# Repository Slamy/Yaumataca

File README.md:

# Yet another USB mouse and joystick to Amiga, Atari ST &amp; C64 Adapter

Or in short Yaumataca. This device allows to use modern USB input devices
on 80s style home computer controller ports. Being mechanical in nature, old gamepads and mouses
degrade over time and replacements using modern variants might be required.

This solution makes use of the Raspberry Pi Pico board (RP2040) which offers a dedicated USB host controller
and can be bought at a rather low price (5-8€ per unit).
Cheap NPN transistors are used for level shifting as the RP2040 is not 5V tolerant.

## How to use

The Yaumataca acts as both Joystick and Mouse. Plug both output ports into both controller ports of the target machine.
Plug a USB OTG Hub into the Micro-USB port of the Pico board. Insert USB gamepad and USB mouse.

As multiple modes are supported, the [user manual](doc/user_manual.md) provides more detail.

## Features
* Cheap to build
* Uses "off the shelf" hardware
* Multiple USB devices on 2 Atari type controller ports using a single unit
* Primary joystick on left port
* Primary mouse on right port
* Amiga mouse with wheel using [WheelBusMouse](http://aminet.net/package/util/mouse/WheelBusMouse) driver
* Commodore 1351 in proportional mode
* Atari ST mouse
* Automatic switch between mouses and joysticks
* Swap of controller ports (useful for C64 games)
* Supports 2 mouses and 2 joysticks (useful for Lemmings and Marble Madness)
* Supports secondary fire button (Amiga and C64 style)
* Auto fire
* Configured mouse type is saved in flash

## Restrictions
* Only dedicated Joysticks are supported.
	* PS3 DualShock
	* PS4 DualShock
	* Nintendo Switch Pro Controller
	* Xbox 360 Wireless Receiver (1 or 2 controllers with one receiver)
	* Xbox One Controller
	* Xbox Series S/X Controller
	* Mega World International - USB Game Controllers (07b5:0314)
	* DragonInc Hizue Gamepad (0079:0011)

## TODO
* Amiga Mode: Add support for newmouse or Micromys protocol
	* Avoids necessity for manipulation of the unrelated joystick port
* Add 3. Fire button for more gamepads
* HID Descriptor Parsing (generic USB joystick support, eventually)
* Bluetooth (eventually)
* Explain C1351 calibration using C64 tool

## How to construct

The project is constructable via perfboard or PCB.

[Manual for construction on a perfboard](doc/construction_perfboard.md)

For the PCB, please use the [KiCad files](schematic/yaumataca/).
If you order your parts from [Reichelt](https//reichelt.de), you may use the
attached [ordering lists](doc/reichelt.csv) which can be imported on the website.

In case the PCB is chosen, there is also a [3D model of a case](housing/) available, which can be used for 3D printing.

To operate the unit, one OTG Hub is recommended which provides multiple USB A ports attached to a USB micro port.
If only one USB device is to be attached, a simple USB micro to USB A adapter will also work, but I suggest to go for the Hub.

### Example hardware design

Here an example of the PCB inside the case.

Here the PCB side by side with the prototype.

## How to build the firmware

Ensure that the submodules are also cloned.

	git submodule update --init --recursive
	mkdir build
	cd build
	cmake ..
	make

Alternatively there is also a small script which builds and packages the software as a zip file for upload.

	./scripts/build_release.sh

## How to flash

### Integrated USB bootloader

The RP2040 can be flashed using SWD or using the integrated USB bootloader.
As not everyone might have a debugger lying around, flash the Pico as so:

* Don't have the Pico board powered and connected.
* Press and hold the BOOTSEL button
* Connect the Pico to your PC while holding the button
* The Pico should be detected as mass storage device
* Copy `yaumataca.uf2` from the `build` folder to the device
* The LED of the Pico should start blinking

The Yaumataca is now ready for operation

### With SWD

This assumes that you are using a CMSIS-DAP compatible programmer. It is suggested to use a second Pico board as one.
This is possible using [the Picoprobe firmware](https://github.com/raspberrypi/picoprobe/releases).
Keep in mind that an st-link cannot be used with the RP2040, even so both speak SWD.

	openocd -f interface/cmsis-dap.cfg -f target/rp2040.cfg -c "adapter speed 20000; program build/yaumataca.elf verify reset exit"

Connect the picoprobe like so, to flash and debug the Yaumataca in standalone operation:

Keep in mind to only connect 5V (purple wire) when operating the Yaumataca without any home computer attached!
The 5V power supply is usually provided by the controller port and not from the PC!
It must not be delivered by both the developer PC and the homecomputer at the same time!

## Recommended IDE

Please use vscode and open the root folder with it.
This gives access to the already existing debugging targets.

## System architecture

## Doxygen and Unittests

It is my goal to have everything properly documented and tested

	scripts/check_doxygen.sh
	scripts/unittest.sh

## FAQ

### My gamepad is not supported. What can I do?

It depends. Some USB Gamepads are not following the HID standard, which is a huge
issue. The PS4 Controller is one rare exception which just works.
Bad examples are the Xbox One Controller and the Nintendo Switch Pro Controller.

Both require some sort of handshaking to activate the data transfer.

If you are lucky, you have a USB input device which just follows the HID standard.

[Please follow this guide to add additional gamepads](doc/adding_gamepads.md)

### I can see PRINTF all over the place. Where is the output going to?

This project makes use of "Segger RTT" which stores printed characters
inside a small buffer which can be displayed over SWD.
It has advantages compared to the UART as no additional GPIOs
have to be reserved for this.

I don't recommend to use rtthost as it is slow. Please use VSCode instead.

	rtthost -c rp2040

There is also pyocd available, which is faster:

	pyocd rtt --target rp2040

### SWD is failing with "Info : DAP init failed"

You have accidentally downloaded `debugprobe` and not `picoprobe`.
This project uses the CMSIS-DAP variant of the picoprobe!
One working version is [this one](https://github.com/raspberrypi/debugprobe/releases/tag/picoprobe-cmsis-v1.1).

### I can't use the C1351 mouse on "Final Cartridge III"

The design of the Yaumataca circuit might not be optimal, as it causes issues with the
way the FC3 software is using the SID muxes in desktop mode. For some reason, both Controller Ports
are muxed at the same time to the SIDs POT lines, so it can accept a mouse at either of the ports
without additional configuration. This however means that no two mice are allowed to be connected
at the same time.

The Yaumataca design is not aware of this and uses a 10k pullup on POT X and POT Y to charge the measurement capacitor.
This alone is not an issue. However, with the addition of the secondary fire buttons on the C64,
this indeed causes issues as the high state is the pressed state while the grounded state
is not pressed. This is opposite to how the Amiga handles its buttons.

If this issue occurs, just disconnect one of the controller ports.

### Why is this not written in Rust?

Because USB Host Support for the RP2040 is not yet awesome

### Isn't this yet another USB mouse and joystick to Amiga, Atari ST & C64 adapter

Exactly

### Funny anecdote

The popularity of this project was increased dramatically just becausean Atari ST
user was missing a mouse on a Commodore 64 party.
This happened on the DoReCo (Dortmund Retro Computer) Party 2024 in Anröche, Germany.

## Sources of Inspiration

My old project this here needs to surpass:<br>
http://slamyslab.blogspot.com/2013/02/pcbs-for-usb-datasette-and.html

Infos about Mouse Wheels on the Amiga:<br>
http://bax.comlab.uni-rostock.de/en/hardware/amiga-usb-mouse/

For the pinout:<br>
https://www.c64-wiki.de/wiki/Maus

Information about the Commodore 1351:<br>
http://sensi.org/~svo/%5Bm%5Douse/

Micromys C64 and Amiga Mouse Protocol:<br>
https://wiki.icomp.de/wiki/Micromys_Protocol

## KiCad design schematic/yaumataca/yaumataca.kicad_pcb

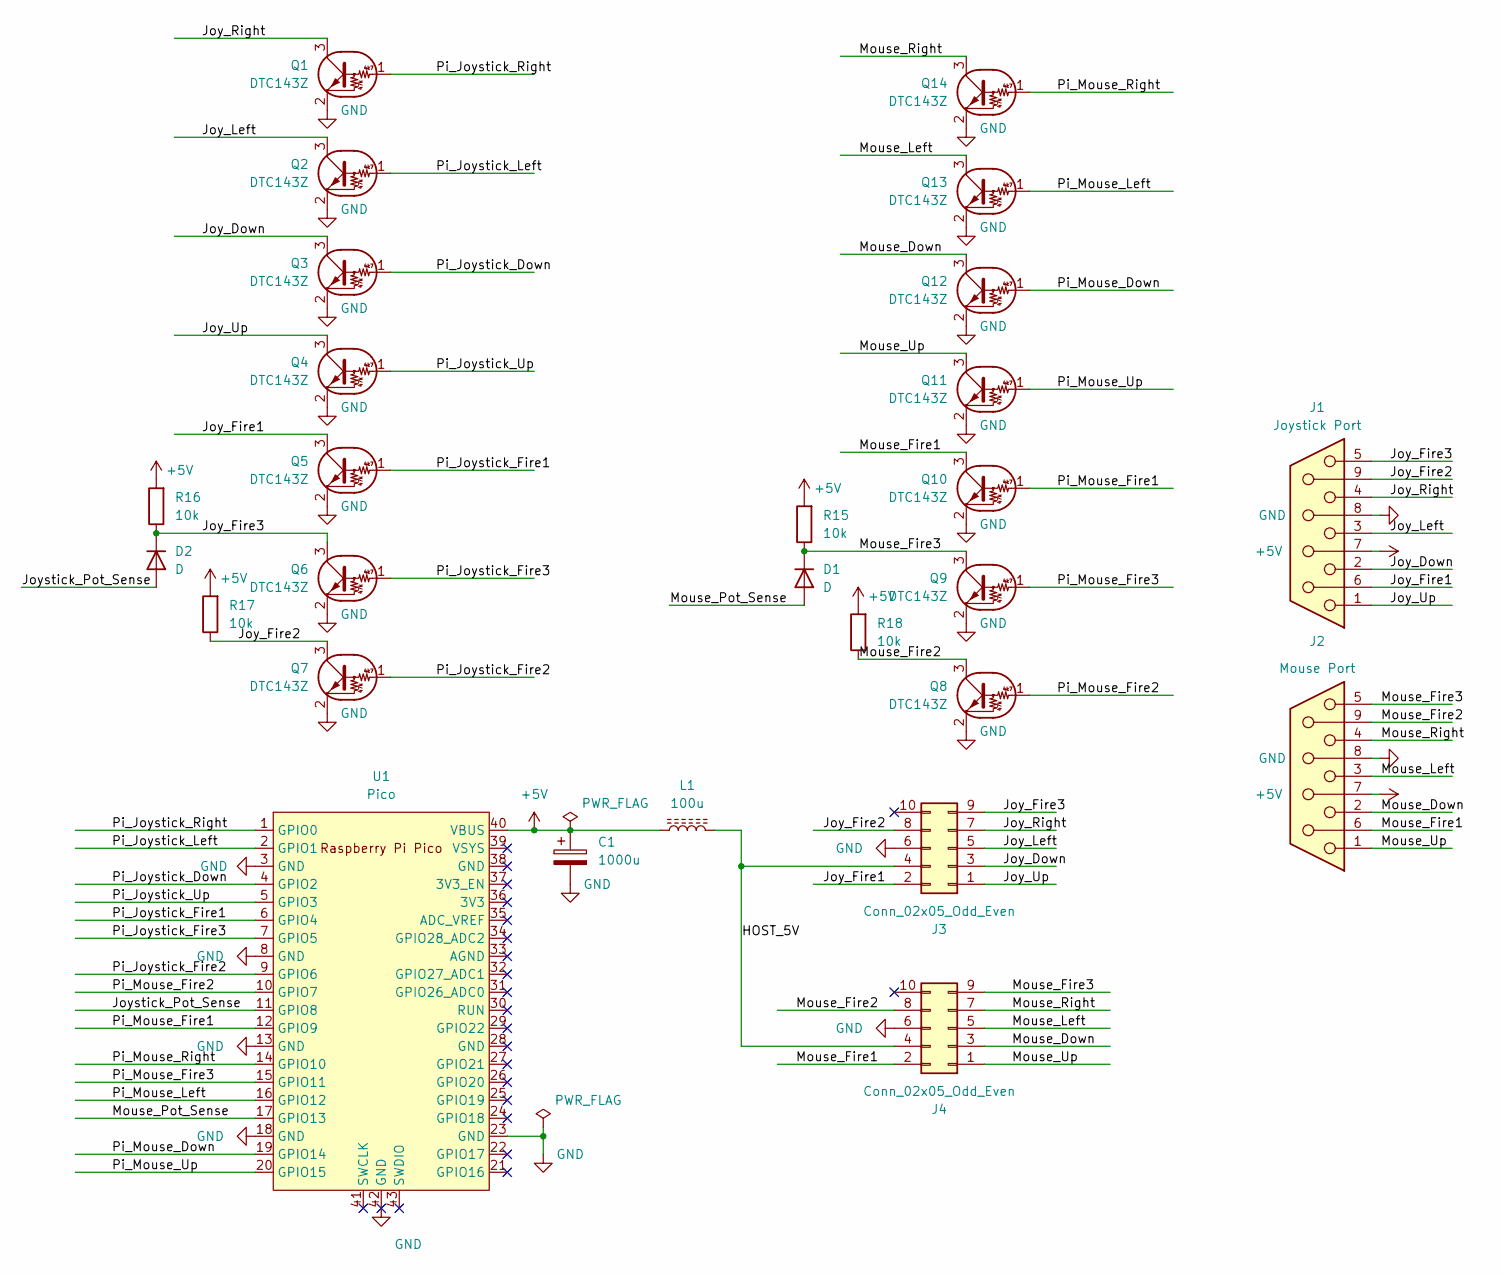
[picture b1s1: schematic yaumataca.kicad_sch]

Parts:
C1: 1000u; CP_Radial_D10.0mm_P5.00mm
D1, D2: D; D_SOD-123
J1: Joystick Port; DSUB-9_Female_Horizontal_P2.77x2.84mm_EdgePinOffset4.94mm_H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
J2: Mouse Port; DSUB-9_Female_Horizontal_P2.77x2.84mm_EdgePinOffset4.94mm_H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
J3, J4: Conn_02x05_Odd_Even; IDC-Header_2x05_P2.54mm_Vertical
L1: 100u; L_Axial_L5.3mm_D2.2mm_P7.62mm_Horizontal_Vishay_IM-1
Q1, Q2, Q3, Q4, Q5, Q6, Q7, Q8, Q9, Q10, Q11, Q12, Q13, Q14: DTC143Z; SOT-23_ohnesilk
R15, R16, R17, R18: 10k; R_0805_2012Metric_Pad1.20x1.40mm_HandSolder
U1: Pico; RPi_Pico_SMD_TH

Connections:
+5V: C1.1, J1.7, J2.7, L1.1, R15.2, R16.2, R17.2, R18.2, U1.40 (VBUS)
/HOST_5V: J3.4, J4.4, L1.2
/Joy_Down: J1.2, J3.3, Q3.3 (C)
/Joy_Fire1: J1.6, J3.2, Q5.3 (C)
/Joy_Fire2: J1.9, J3.8, Q7.3 (C), R17.1
/Joy_Fire3: D2.1 (K), J1.5, J3.9, Q6.3 (C), R16.1
/Joy_Left: J1.3, J3.5, Q2.3 (C)
/Joy_Right: J1.4, J3.7, Q1.3 (C)
/Joy_Up: J1.1, J3.1, Q4.3 (C)
/Joystick_Pot_Sense: D2.2 (A), U1.11 (GPIO8)
/Mouse_Down: J2.2, J4.3, Q12.3 (C)
/Mouse_Fire1: J2.6, J4.2, Q10.3 (C)
/Mouse_Fire2: J2.9, J4.8, Q8.3 (C), R18.1
/Mouse_Fire3: D1.1 (K), J2.5, J4.9, Q9.3 (C), R15.1
/Mouse_Left: J2.3, J4.5, Q13.3 (C)
/Mouse_Pot_Sense: D1.2 (A), U1.17 (GPIO13)
/Mouse_Right: J2.4, J4.7, Q14.3 (C)
/Mouse_Up: J2.1, J4.1, Q11.3 (C)
/Pi_Joystick_Down: Q3.1 (B), U1.4 (GPIO2)
/Pi_Joystick_Fire1: Q5.1 (B), U1.6 (GPIO4)
/Pi_Joystick_Fire2: Q7.1 (B), U1.9 (GPIO6)
/Pi_Joystick_Fire3: Q6.1 (B), U1.7 (GPIO5)
/Pi_Joystick_Left: Q2.1 (B), U1.2 (GPIO1)
/Pi_Joystick_Right: Q1.1 (B), U1.1 (GPIO0)
/Pi_Joystick_Up: Q4.1 (B), U1.5 (GPIO3)
/Pi_Mouse_Down: Q12.1 (B), U1.19 (GPIO14)
/Pi_Mouse_Fire1: Q10.1 (B), U1.12 (GPIO9)
/Pi_Mouse_Fire2: Q8.1 (B), U1.10 (GPIO7)
/Pi_Mouse_Fire3: Q9.1 (B), U1.15 (GPIO11)
/Pi_Mouse_Left: Q13.1 (B), U1.16 (GPIO12)
/Pi_Mouse_Right: Q14.1 (B), U1.14 (GPIO10)
/Pi_Mouse_Up: Q11.1 (B), U1.20 (GPIO15)
GND: C1.2, J1.8, J2.8, J3.6, J4.6, Q1.2 (E), Q2.2 (E), Q3.2 (E), Q4.2 (E), Q5.2 (E), Q6.2 (E), Q7.2 (E), Q8.2 (E), Q9.2 (E), Q10.2 (E), Q11.2 (E), Q12.2 (E), Q13.2 (E), Q14.2 (E), U1.3 (GND), U1.8 (GND), U1.13 (GND), U1.18 (GND), U1.23 (GND), U1.42 (GND)

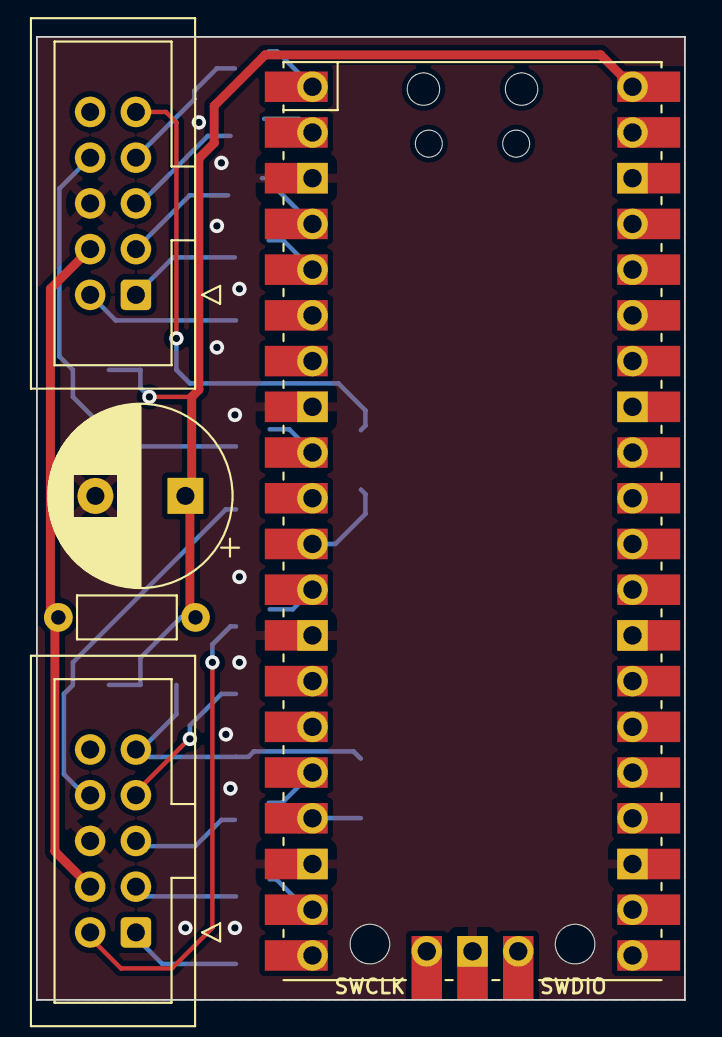
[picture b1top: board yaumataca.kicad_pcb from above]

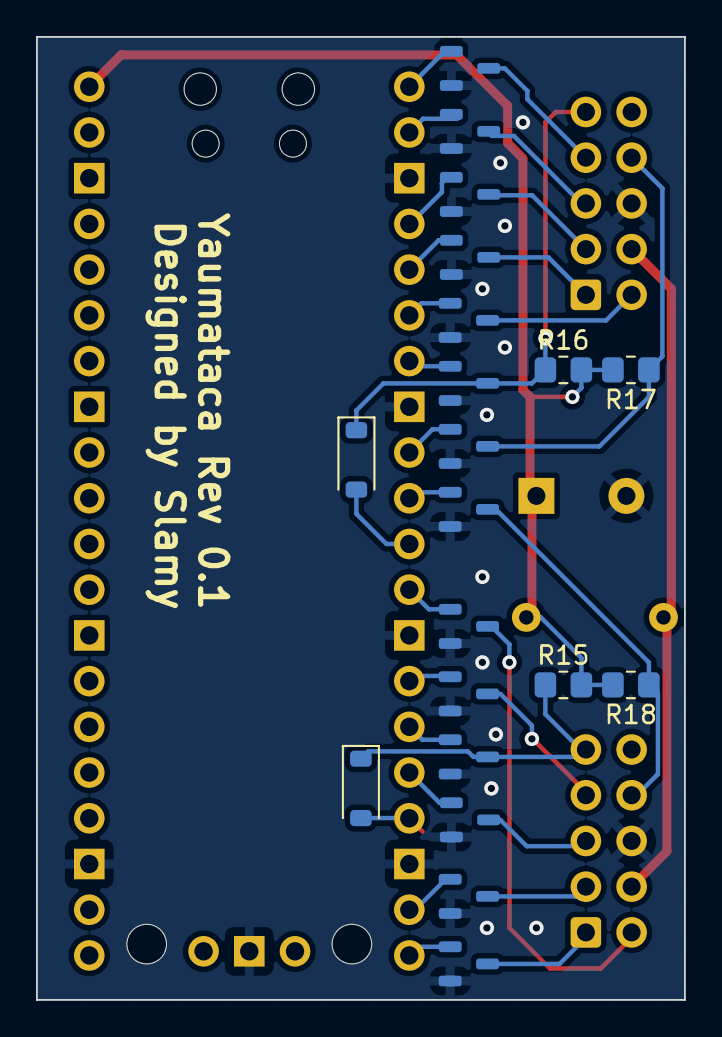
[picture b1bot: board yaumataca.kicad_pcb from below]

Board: 2 copper layers, 36.0 x 53.5 mm, 25 parts (20 on the bottom side), 33 nets.

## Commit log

2023-08-05 First working release of the software
    One Amiga mouse and one Joystick supported.
2023-08-14 Implemented most features
    C1351 emulation via PIO.
    Added basic unit test.
    Added first doxygen project config.
    Added auto fire handling.
    Added pipeline concept for the various components.
    Mouse mode switching via user button.
2023-08-16 Fixed Amiga signal stability
2023-08-16 Added flash eeprom emulation
2023-08-16 Fixed wrong constructor in pipeline.
    Also don't write config if unchanged
2023-08-16 Adapted README
2023-08-16 removed debugging prints
2023-08-18 Doxygen documentation
2023-08-18 Added Switch Pro Controller
    Implemented custom handshaking protocol
    Refined report reception for multiple classes
    Auto fire is also faster
2023-08-24 Unit tests Fixed unit tests
2023-08-24 Test on Atari ST
    for the first time.
    Reduced frequency.
2023-08-30 Documentation
    Just a little bit more text.
    Also updated schematics and created
    some diagrams.
2023-08-30 Added analog stick of PS3 controller
2023-08-31 Added system architecture
    via PlantUML
2023-09-08 Fixing shadowing of global declaration
    Required for GCC 12.2.1
2024-02-16 Cleanup of impact joystick
    with packed structs
2024-02-16 Added PS4 dualshock
    just the tinyusb example
2024-02-16 Applied different code style
    Also cleanup of ps3 controller
2024-02-16 Bare Api and Xbox One Controller
    Supports vendor class interfaces
    using bare api.
    But I do have the feeling that this
    is sometimes unstable...
2024-02-16 tinyusb update to recent master
2024-02-16 Add C1351 calibration mode
    Comes with small tool for c64
2024-02-21 First idea of a PCB
    All components on one side
2024-02-21 Added revision silkscreen
    It was missing from the order.
    No other change to the circuit
2024-02-21 Added ordered PCB
    Components on both sides for an
    even smaller size.
2024-02-21 doxygen fixes
2024-03-13 added first revision of housing
2024-03-22 Fixed muxing configuration timing
2024-03-22 Unit test fixes
2024-03-22 Use wheel instead of mouse during calibration
    more precision
2024-03-22 Fixed secondary fire on other port
    Also improved calibration method
2024-05-20 added second revision of housing
    improved mechanical stability
    button is now an actual button instead
    of just a hole
    fixed missing hole in PCB for the screw
2024-05-22 Added reichelt order list
2024-10-04 Temporary removal of "Set Report" for mice
    Avoids compatibility issues with
    more complex HID reports
2024-10-04 Always depress 3rd fire button in c64 mode
2024-10-05 Test software for trb
2024-10-07 Experimental Xbox controller
2024-10-12 Experimental PS4 controller
2024-10-16 Experimental PS3 controller
2024-11-30 Fixed documentation
    The pinout diagram was not correct,
    after it was adapted for an easier PCB design.
2024-11-30 Added support for a third fire button
2024-11-30 Added additional mouse swap mode
    Controller port swapping can now
    also be performed using 2 buttons instead of all 3.
    This should help with 2 button mice.
2024-11-30 Additional PS4 controller VID PID combos
2024-11-30 Additional Xbox controller VID PID combos
2024-11-30 Additional PS3 controller VID PID combo
2024-11-30 Added HID Report Parser for Mice
    Fixes mice with more complex HID reports
    than the usual boot mode with one wheel byte
    at the end.
2024-11-30 Add release build script
    To make packaging everything for github
    a little bit easier.
    Also added additional readme info.
2024-11-30 Documentation about adding devices
    # Conflicts:
    # README.md
2024-11-30 Added DragonInc Hizue pad
    Thanks to Spacepilot3000 for providing report data
2024-11-30 Added DragonInc Hizue pad
    Thanks to Spacepilot3000 for providing report data
    Also removed subfolders from release file
2024-11-30 Documentation about adding devices
    A basic idea by Forum64 to get more people into the project
    Needs to be tested by a second person though
2024-12-01 Added Final Cart III hack
    The FC3 module muxes both controller
    ports to the POT lines of the SID.
    It is incompatible with two mice
    and the way, the Yaumataca simulates
    a C1351. This hack enforces to "let go"
    of these lines which indirectly might
2024-12-01 Added C64 Micromys Wheel
    It uses the left and right direction signals
    Also added another release binary
    with Amiga wheel target being disabled.
2024-12-04 Change of boot up configuration
    Primary mouse port now starts as a mouse.
    Previously everything started as a joystick.
    Fixes Final Cart III after power cycle as the desktop
    mode is searching for a mouse.
    Also cleanup of debugging output
2024-12-04 Resolve empty port after unplug
    With two joysticks and one mouse,
    it should be expected to separate
    the remaining devices after unplugging
    one.
2024-12-30 Fixed switching source reference
    during reattachment of input source.
    It has caused 2 input sources to share one
    primary switcher
2024-12-30 Added support for Xbox 360 Wireless Receiver
    Thanks to quadflyer8 for providing testing hardware
    Two Xbox 360 Wireless controllers are supported
    at the same time
2025-01-04 Added new controller to readme
2025-01-05 Added changelog
